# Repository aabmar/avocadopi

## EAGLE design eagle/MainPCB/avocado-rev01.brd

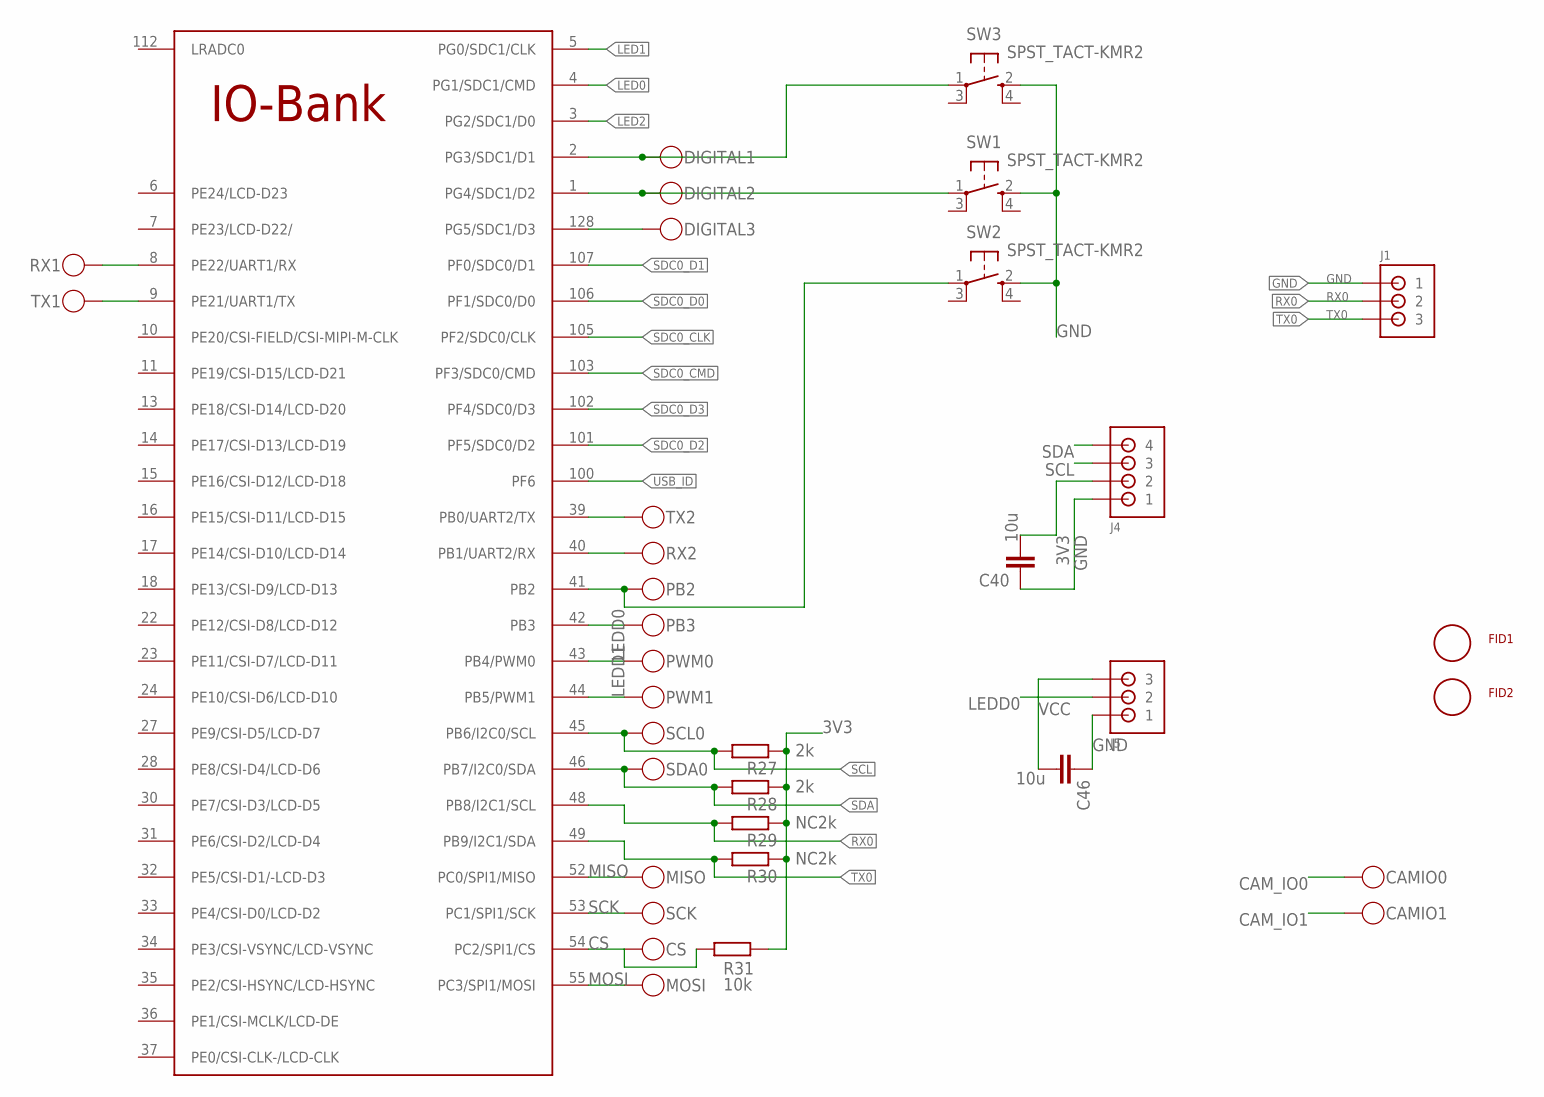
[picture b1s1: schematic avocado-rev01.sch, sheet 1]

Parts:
C40, C46: 10u; C0603
CAMIO0, CAMIO1: TEST_TESTPOINT
CS: TEST_TESTPOINT
DIGITAL1, DIGITAL2, DIGITAL3: TEST_TESTPOINT
FID1, FID2: FIDUCIAL; FIDUCIAL_1MM
J1, J5: CONNECTOR-3HEADER3; HEADER-3
J4: CONNECTOR-4HEADER4; HEADER-4
MISO: TEST_TESTPOINT
MOSI: TEST_TESTPOINT
PB2, PB3: TEST_TESTPOINT
PWM0, PWM1: TEST_TESTPOINT
R27, R28: 2k; R0402
R29, R30: NC2k; R0402
R31: 10k; R0402
RX1, RX2: TEST_TESTPOINT
SCK: TEST_TESTPOINT
SCL0: TEST_TESTPOINT
SDA0: TEST_TESTPOINT
SW1, SW2, SW3: SPST_TACT-KMR2; KMR2
TX1, TX2: TEST_TESTPOINT
U1: V3S; QFP-128

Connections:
3V3: C40.2, J4.2, R27.1, R28.1, R29.1, R30.1, R31.1; also elsewhere on the board
CAM_IO0: CAMIO0.1; also elsewhere on the board
CAM_IO1: CAMIO1.1; also elsewhere on the board
CS: CS.1, R31.2, U1.54 (PC2/SPI1/CS)
GND: C40.1, C46.1, J1.1, J4.1, J5.1, SW1.2 (S), SW2.2 (S), SW3.2 (S); also elsewhere on the board
LED0: U1.4 (PG1/SDC1/CMD); also elsewhere on the board
LED1: U1.5 (PG0/SDC1/CLK); also elsewhere on the board
LED2: U1.3 (PG2/SDC1/D0); also elsewhere on the board
LEDD0: J5.2, PWM0.1, U1.43 (PB4/PWM0); also elsewhere on the board
LEDD1: PWM1.1, U1.44 (PB5/PWM1); also elsewhere on the board
MISO: MISO.1, U1.52 (PC0/SPI1/MISO)
MOSI: MOSI.1, U1.55 (PC3/SPI1/MOSI)
unnamed: RX2.1, U1.40 (PB1/UART2/RX)
unnamed: PB2.1, SW2.1, U1.41 (PB2)
unnamed: PB3.1, U1.42 (PB3)
unnamed: DIGITAL1.1, SW3.1, U1.2 (PG3/SDC1/D1)
unnamed: DIGITAL2.1, SW1.1, U1.1 (PG4/SDC1/D2)
unnamed: DIGITAL3.1, U1.128 (PG5/SDC1/D3)
RX0: J1.2, R29.2, U1.48 (PB8/I2C1/SCL)
RX1: RX1.1, U1.8 (PE22/UART1/RX)
SCK: SCK.1, U1.53 (PC1/SPI1/SCK)
SCL: J4.3, R27.2, SCL0.1, U1.45 (PB6/I2C0/SCL); also elsewhere on the board
SDA: J4.4, R28.2, SDA0.1, U1.46 (PB7/I2C0/SDA); also elsewhere on the board
SDC0_CLK: U1.105 (PF2/SDC0/CLK); also elsewhere on the board
SDC0_CMD: U1.103 (PF3/SDC0/CMD); also elsewhere on the board
SDC0_D0: U1.106 (PF1/SDC0/D0); also elsewhere on the board
SDC0_D1: U1.107 (PF0/SDC0/D1); also elsewhere on the board
SDC0_D2: U1.101 (PF5/SDC0/D2); also elsewhere on the board
SDC0_D3: U1.102 (PF4/SDC0/D3); also elsewhere on the board
TX0: J1.3, R30.2, U1.49 (PB9/I2C1/SDA)
TX1: TX1.1, U1.9 (PE21/UART1/TX)
TX2: TX2.1, U1.39 (PB0/UART2/TX)
USB_ID: U1.100 (PF6); also elsewhere on the board
VCC: C46.2, J5.3; also elsewhere on the board

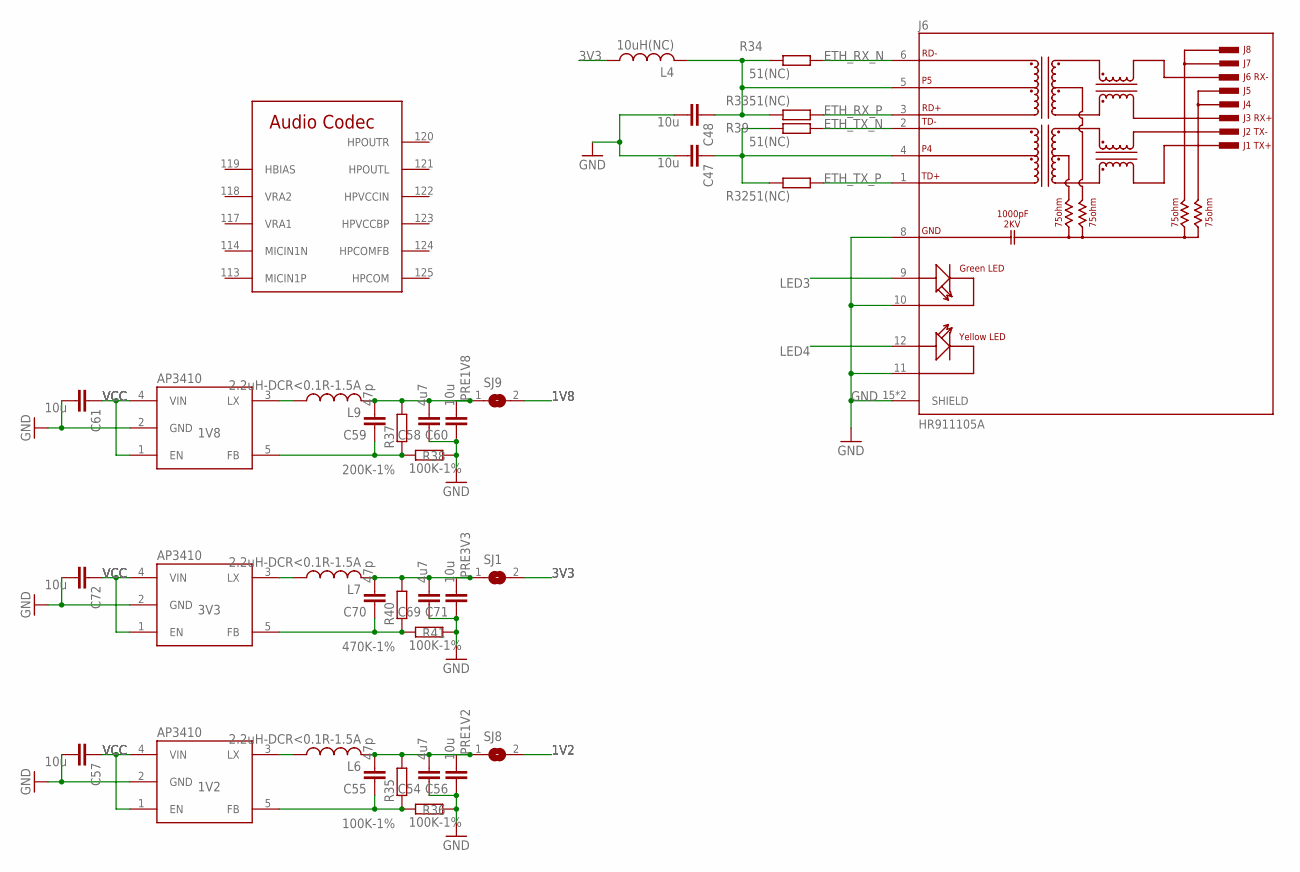
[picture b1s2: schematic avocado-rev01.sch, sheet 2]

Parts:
C47, C48, C56, C57, C60, C61, C71, C72: 10u; C0603
C54, C58, C69: 4u7; C0603
C55, C59, C70: 47p; C0603
IC2: 3V#; SOT23-5L; VOLTAGE 3V3; MPN AP3410KTR-G1
IC5: 3V#; SOT23-5L; VOLTAGE 1V2
IC6: MCP73811/2; SOT23-5L; VOLTAGE 1V8; MPN AP3410KTR-G1
J6: HR911105A; HANRUN_HR911105A
L4: 10uH(NC); R0603; MPN LVF404018-2R2M-N
L6, L7, L9: 2.2uH-DCR<0.1R-1.5A; ASPI-4030S-253675; MPN LVF404018-2R2M-N; MOUSER LVF404018-2R2M-N
R32, R33, R34, R39: 51(NC); R0402
R35, R36, R38, R41: 100K-1%; R0402
R37: 200K-1%; R0402
R40: 470K-1%; R0402
SJ1, SJ8, SJ9: SJ
U1: V3S; QFP-128

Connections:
1V2: SJ8.2; also elsewhere on the board
1V8: SJ9.2; also elsewhere on the board
3V3: L4.1, SJ1.2; also elsewhere on the board
ETH_RX_N: J6.6 (RD-), R34.1; also elsewhere on the board
ETH_RX_P: J6.3 (RD+), R33.1; also elsewhere on the board
ETH_TX_N: J6.2 (TD-), R39.1; also elsewhere on the board
ETH_TX_P: J6.1 (TD+), R32.1; also elsewhere on the board
GND: C47.2, C48.2, C54.1, C56.1, C57.2, C58.1, C60.1, C61.2, C69.1, C71.1, C72.2, IC2.2 (GND), IC5.2 (GND), IC6.2 (GND), J6.8 (GND), J6.10 (GC), J6.11 (YC), J6.15 (SHIELD), J6.16 (SHIELD), R36.2, R38.2, R41.2; also elsewhere on the board
LED3: J6.9 (GA); also elsewhere on the board
LED4: J6.12 (YA); also elsewhere on the board
unnamed: IC2.3 (LX), L7.P$1 (1)
unnamed: C70.1, IC2.5 (FB), R40.1, R41.1
unnamed: IC5.3 (LX), L6.P$1 (1)
unnamed: C55.1, IC5.5 (FB), R35.1, R36.1
unnamed: IC6.3 (LX), L9.P$1 (1)
unnamed: C59.1, IC6.5 (FB), R37.1, R38.1
unnamed: C47.1, J6.4, R32.2, R39.2
unnamed: C48.1, J6.5, L4.2, R33.2, R34.2
PRE1V2: C54.2, C55.2, C56.2, L6.P$2 (2), R35.2, SJ8.1
PRE1V8: C58.2, C59.2, C60.2, L9.P$2 (2), R37.2, SJ9.1
PRE3V3: C69.2, C70.2, C71.2, L7.P$2 (2), R40.2, SJ1.1
VCC: C57.1, C61.1, C72.1, IC2.1 (EN), IC2.4 (VIN), IC5.1 (EN), IC5.4 (VIN), IC6.1 (EN), IC6.4 (VIN); also elsewhere on the board

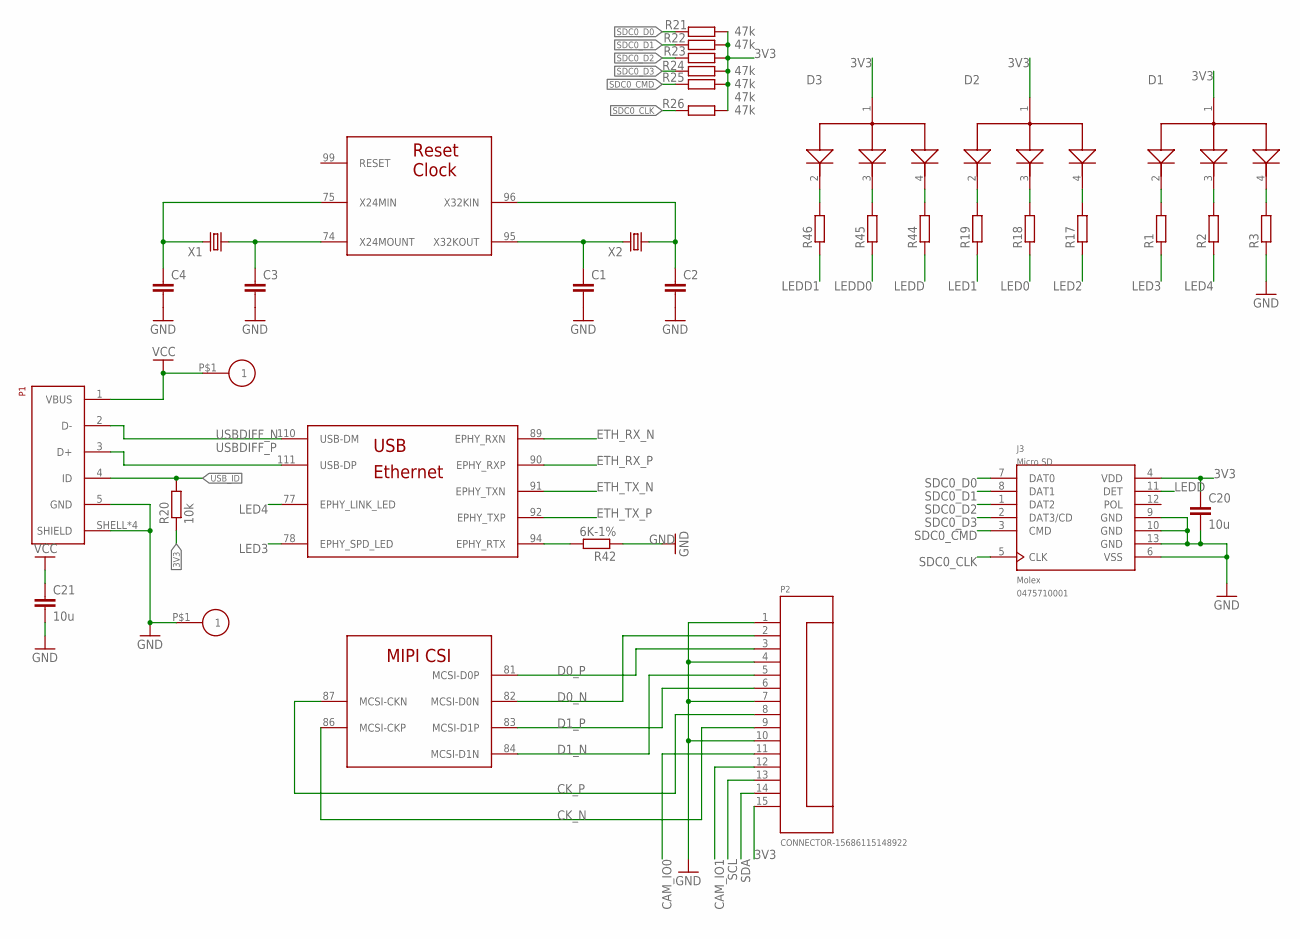
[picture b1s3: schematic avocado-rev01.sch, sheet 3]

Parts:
5V: PADTH; PAD
C1, C2, C3, C4: C0603
C20, C21: 10u; C0603
D1, D2, D3: LL-R3528RGBC-008-B; LED_LL-R3528RGBC-008-B; MPN HQ67-23A2ARGBC
GND: PADTH; PAD
J3: 0475710001; MOLEX_0475710001
P1: USB629105150521; 629105150521
P2: CONNECTOR-15686115148922; 686115148922
R1, R2, R3, R17, R18, R19, R44, R45, R46: R-EU_R0402; R0402
R20: 10k; R0402
R21, R22, R23, R24, R25, R26: 47k; R0603
R42: 6K-1%; R0402
U1: V3S; QFP-128
X1: XTAL3.2X2; 3.2X2-4; MPN 7U24000E09UCG
X2: XTAL5X1.9; XTAL-5X1.9; MPN SF32K32768D71T01

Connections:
3V3: C20.1, D1.1 (COMM_ANODE), D2.1 (COMM_ANODE), D3.1 (COMM_ANODE), J3.4 (VDD), P2.15, R20.1, R21.2, R22.2, R23.2, R24.2, R25.2, R26.2; also elsewhere on the board
CAM_IO0: P2.11; also elsewhere on the board
CAM_IO1: P2.12; also elsewhere on the board
CK_N: P2.9, U1.86 (MCSI-CKP)
CK_P: P2.8, U1.87 (MCSI-CKN)
D0_N: P2.2, U1.82 (MCSI-D0N)
D0_P: P2.3, U1.81 (MCSI-D0P)
D1_N: P2.5, U1.84 (MCSI-D1N)
D1_P: P2.6, U1.83 (MCSI-D1P)
ETH_RX_N: U1.89 (EPHY_RXN); also elsewhere on the board
ETH_RX_P: U1.90 (EPHY_RXP); also elsewhere on the board
ETH_TX_N: U1.91 (EPHY_TXN); also elsewhere on the board
ETH_TX_P: U1.92 (EPHY_TXP); also elsewhere on the board
GND: C1.2, C2.2, C3.2, C4.2, C20.2, C21.2, GND.P$1, J3.6 (VSS), J3.9 (GND), J3.10 (GND), J3.13 (GND), P1.5 (GND), P1.SHELL (SHIELD), P1.SHELL1 (SHIELD), P1.SHELL2 (SHIELD), P1.SHELL3 (SHIELD), P2.1, P2.4, P2.7, P2.10, R3.1, R42.1; also elsewhere on the board
LED0: R18.1; also elsewhere on the board
LED1: R19.1; also elsewhere on the board
LED2: R17.1; also elsewhere on the board
LED3: R1.1, U1.78 (EPHY_SPD_LED); also elsewhere on the board
LED4: R2.1, U1.77 (EPHY_LINK_LED); also elsewhere on the board
LEDD: J3.11 (DET), R44.1
LEDD0: R45.1; also elsewhere on the board
LEDD1: R46.1; also elsewhere on the board
unnamed: C4.1, U1.75 (X24MIN), X1.P$3 (2)
unnamed: C3.1, U1.74 (X24MOUNT), X1.P$1 (1)
unnamed: C1.1, U1.95 (X32KOUT), X2.P$2 (2)
unnamed: C2.1, U1.96 (X32KIN), X2.P$1 (1)
unnamed: D2.2 (CATHODE_RED), R19.2
unnamed: D2.3 (CATHODE_GREEN), R18.2
unnamed: D2.4 (CATHODE_BLUE), R17.2
unnamed: D1.2 (CATHODE_RED), R1.2
unnamed: D1.3 (CATHODE_GREEN), R2.2
unnamed: D1.4 (CATHODE_BLUE), R3.2
unnamed: R42.2, U1.94 (EPHY_RTX)
unnamed: D3.2 (CATHODE_RED), R46.2
unnamed: D3.3 (CATHODE_GREEN), R45.2
unnamed: D3.4 (CATHODE_BLUE), R44.2
SCL: P2.13; also elsewhere on the board
SDA: P2.14; also elsewhere on the board
SDC0_CLK: J3.5 (CLK), R26.1; also elsewhere on the board
SDC0_CMD: J3.3 (CMD), R25.1; also elsewhere on the board
SDC0_D0: J3.7 (DAT0), R21.1; also elsewhere on the board
SDC0_D1: J3.8 (DAT1), R22.1; also elsewhere on the board
SDC0_D2: J3.1 (DAT2), R23.1; also elsewhere on the board
SDC0_D3: J3.2 (DAT3/CD), R24.1; also elsewhere on the board
USBDIFF_N: P1.2 (D-), U1.110 (USB-DM)
USBDIFF_P: P1.3 (D+), U1.111 (USB-DP)
USB_ID: P1.4 (ID), R20.2; also elsewhere on the board
VCC: 5V.P$1, C21.1, P1.1 (VBUS); also elsewhere on the board

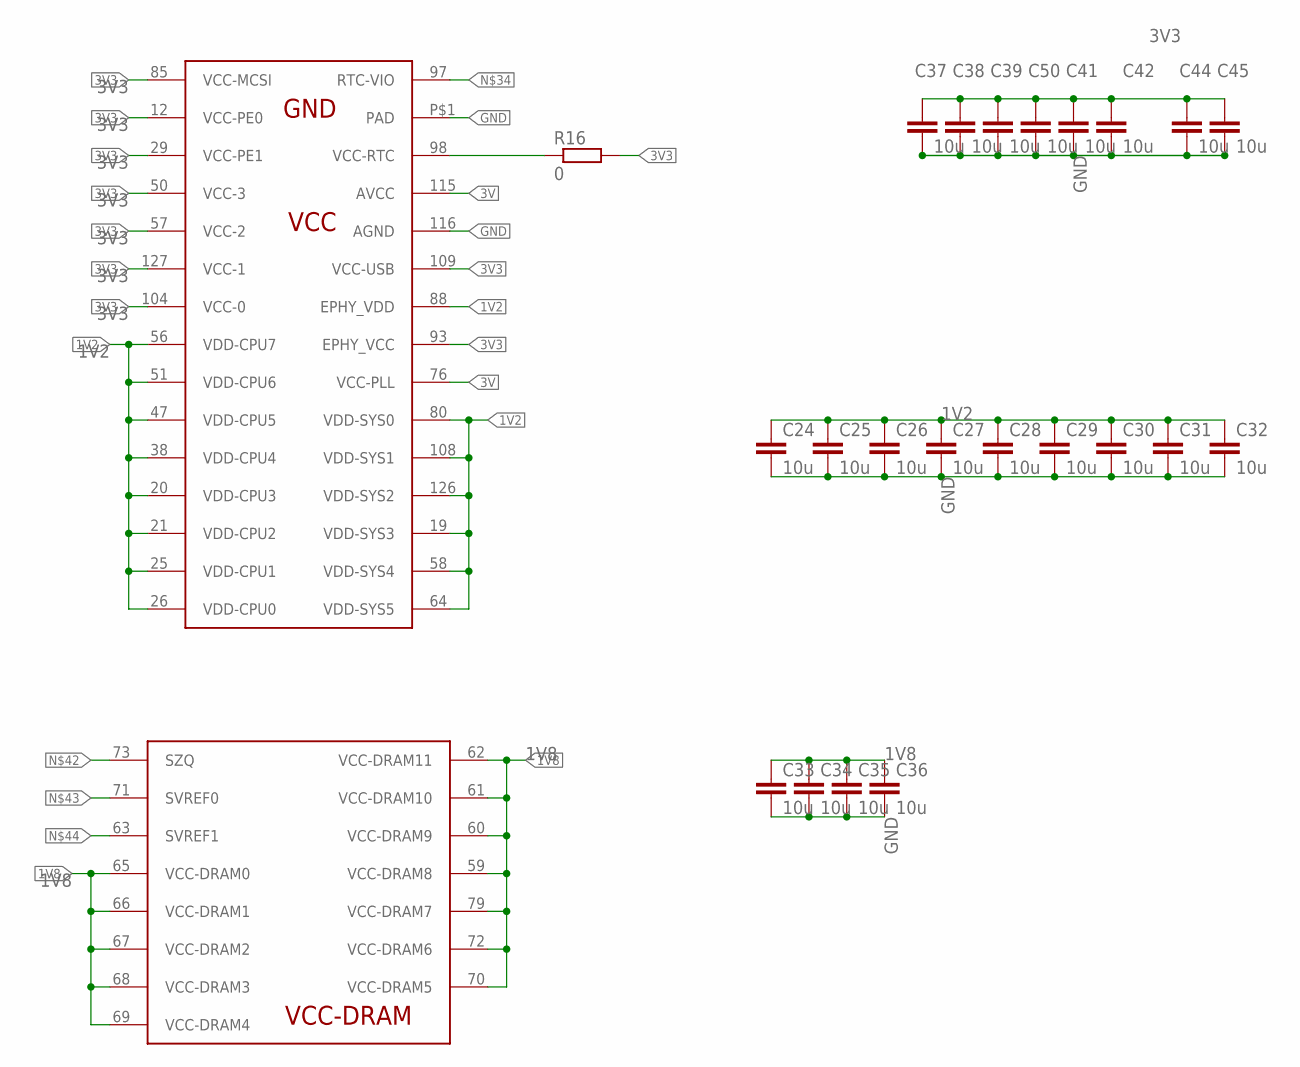
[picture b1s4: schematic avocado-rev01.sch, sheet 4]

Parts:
C24, C25, C26, C27, C28, C29, C30, C31, C32, C33, C34, C35, C36, C37, C38, C39, C41, C42, C44, C45, C50: 10u; C0603
R16: 0; R0603
U1: V3S; QFP-128

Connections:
1V2: C24.1, C25.1, C26.1, C27.1, C28.1, C29.1, C30.1, C31.1, C32.1, U1.19 (VDD-SYS3), U1.20 (VDD-CPU3), U1.21 (VDD-CPU2), U1.25 (VDD-CPU1), U1.26 (VDD-CPU0), U1.38 (VDD-CPU4), U1.47 (VDD-CPU5), U1.51 (VDD-CPU6), U1.56 (VDD-CPU7), U1.58 (VDD-SYS4), U1.64 (VDD-SYS5), U1.80 (VDD-SYS0), U1.88 (EPHY_VDD), U1.108 (VDD-SYS1), U1.126 (VDD-SYS2); also elsewhere on the board
1V8: C33.1, C34.1, C35.1, C36.1, U1.59 (VCC-DRAM8), U1.60 (VCC-DRAM9), U1.61 (VCC-DRAM10), U1.62 (VCC-DRAM11), U1.65 (VCC-DRAM0), U1.66 (VCC-DRAM1), U1.67 (VCC-DRAM2), U1.68 (VCC-DRAM3), U1.69 (VCC-DRAM4), U1.70 (VCC-DRAM5), U1.72 (VCC-DRAM6), U1.79 (VCC-DRAM7); also elsewhere on the board
3V: U1.76 (VCC-PLL), U1.115 (AVCC); also elsewhere on the board
3V3: C37.1, C38.1, C39.1, C41.1, C42.1, C44.1, C45.1, C50.1, R16.2, U1.12 (VCC-PE0), U1.29 (VCC-PE1), U1.50 (VCC-3), U1.57 (VCC-2), U1.85 (VCC-MCSI), U1.93 (EPHY_VCC), U1.104 (VCC-0), U1.109 (VCC-USB), U1.127 (VCC-1); also elsewhere on the board
GND: C24.2, C25.2, C26.2, C27.2, C28.2, C29.2, C30.2, C31.2, C32.2, C33.2, C34.2, C35.2, C36.2, C37.2, C38.2, C39.2, C41.2, C42.2, C44.2, C45.2, C50.2, U1.116 (AGND), U1.P$1 (PAD); also elsewhere on the board
unnamed: R16.1, U1.98 (VCC-RTC)

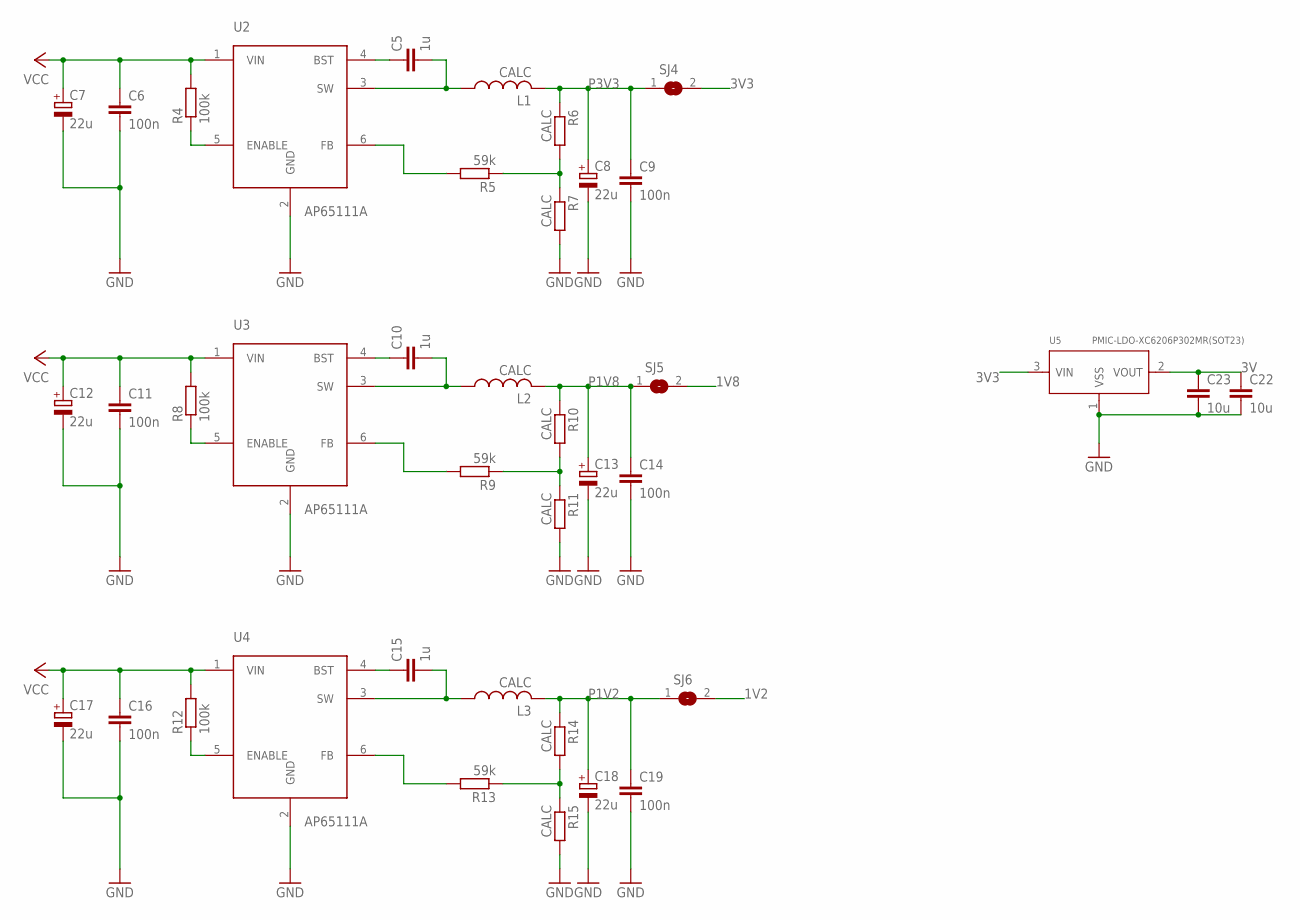
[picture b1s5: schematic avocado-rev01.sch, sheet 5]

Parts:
C5, C10, C15: 1u; C0603
C6, C9, C11, C14, C16, C19: 100n; C0603
C7, C8, C12, C13, C17, C18: 22u; CAP4.3X6.1
C22, C23: 10u; C0603
L1, L2, L3: CALC; B82462A4153K
R4, R8, R12: 100k; R0603
R5, R9, R13: 59k; R0603
R6, R7, R10, R11, R14, R15: CALC; R0603
SJ4, SJ5, SJ6: SJ
U2, U3, U4: AP65111A; TSOT26
U5: PMIC-LDO-XC6206P302MR(SOT23); SOT-23

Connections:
1V2: SJ6.2; also elsewhere on the board
1V8: SJ5.2; also elsewhere on the board
3V: C22.1, C23.1, U5.2 (VOUT); also elsewhere on the board
3V3: SJ4.2, U5.3 (VIN); also elsewhere on the board
GND: C6.2, C7.2 (-), C8.2 (-), C9.2, C11.2, C12.2 (-), C13.2 (-), C14.2, C16.2, C17.2 (-), C18.2 (-), C19.2, C22.2, C23.2, R7.2, R11.2, R15.2, U2.2 (GND), U3.2 (GND), U4.2 (GND), U5.1 (VSS); also elsewhere on the board
unnamed: R5.2, U2.6 (FB)
unnamed: C5.2, L1.P$1 (1), U2.3 (SW)
unnamed: R5.1, R6.2, R7.1
unnamed: C5.1, U2.4 (BST)
unnamed: R4.1, U2.5 (ENABLE)
unnamed: R9.2, U3.6 (FB)
unnamed: C10.2, L2.P$1 (1), U3.3 (SW)
unnamed: R9.1, R10.2, R11.1
unnamed: C10.1, U3.4 (BST)
unnamed: R8.1, U3.5 (ENABLE)
unnamed: R13.2, U4.6 (FB)
unnamed: C15.2, L3.P$1 (1), U4.3 (SW)
unnamed: R13.1, R14.2, R15.1
unnamed: C15.1, U4.4 (BST)
unnamed: R12.1, U4.5 (ENABLE)
P1V2: C18.1 (+), C19.1, L3.P$2 (2), R14.1, SJ6.1
P1V8: C13.1 (+), C14.1, L2.P$2 (2), R10.1, SJ5.1
P3V3: C8.1 (+), C9.1, L1.P$2 (2), R6.1, SJ4.1
VCC: C6.1, C7.1 (+), C11.1, C12.1 (+), C16.1, C17.1 (+), R4.2, R8.2, R12.2, U2.1 (VIN), U3.1 (VIN), U4.1 (VIN); also elsewhere on the board

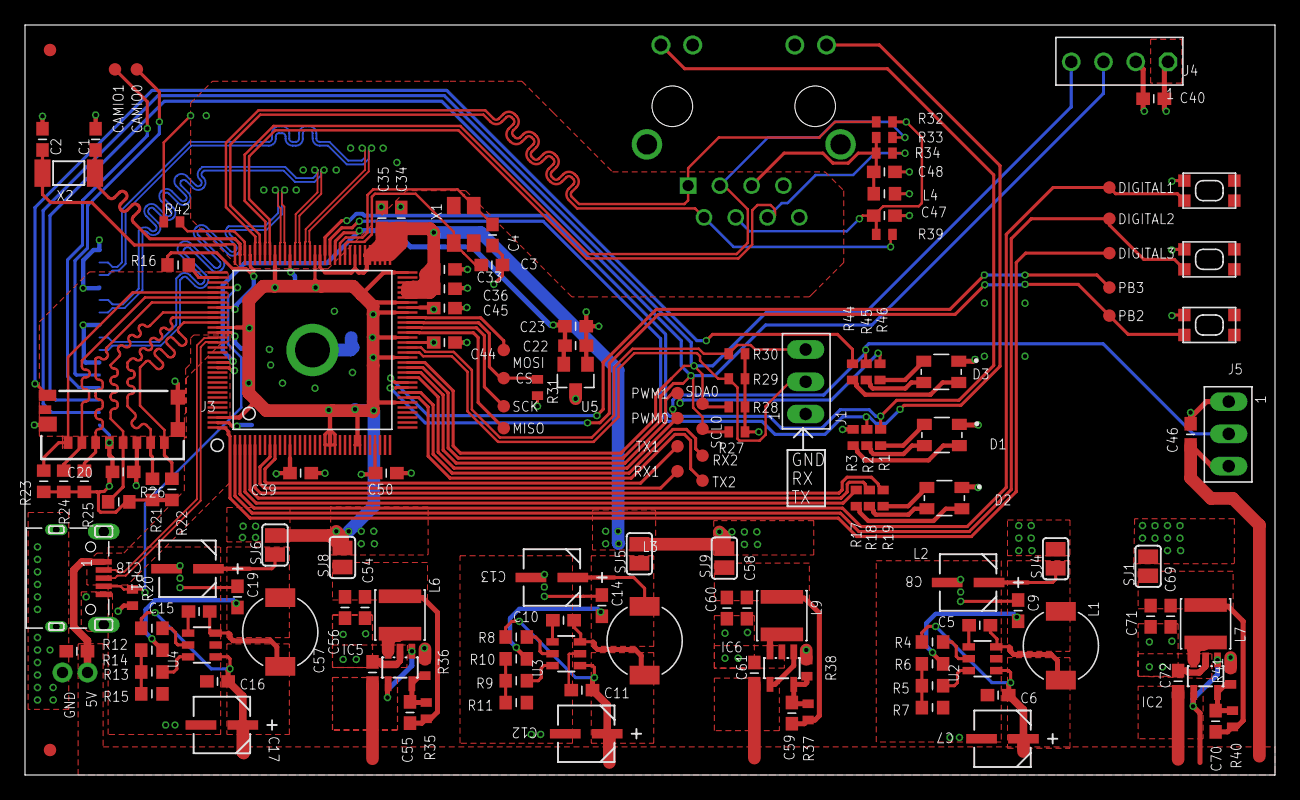
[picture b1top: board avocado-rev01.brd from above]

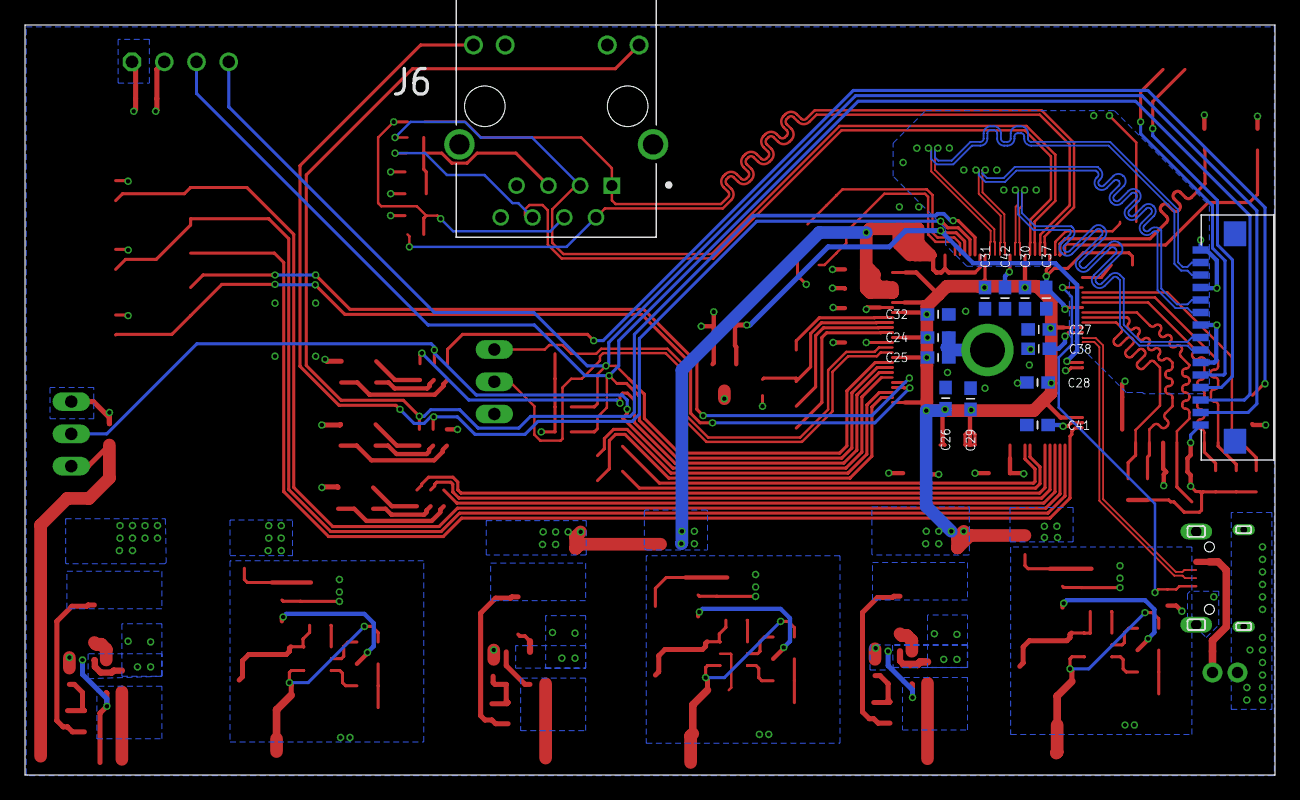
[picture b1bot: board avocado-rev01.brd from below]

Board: 4 copper layers, 100.0 x 60.0 mm, 164 parts (15 on the bottom side), 96 nets.

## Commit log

2019-02-23 Set up Schematics with V3s
2019-02-28 updated schematic
2019-02-28 Connected power
2019-02-28 Removed backup files
2019-03-01 connected sd card and added led
2019-03-01 added testpoints
2019-03-01 updated i2c
2019-03-04 connected psu in schem
2019-03-04 placement
2019-03-04 shitty routing v1
2019-03-06 accurate high speed routing, now 4 layer
2019-03-06 better routing v2
2019-03-06 better routing v3
2019-03-08 decoupling caps
2019-03-11 added 3V rail
2019-03-18 updated decoupling vias
2019-03-19 update keepout area
2019-03-21 add axp209
2019-03-21 updated values
2019-03-25 added jumpers
2019-03-25 high
2019-03-26 Added design rules
2019-03-26 working
2019-03-27 In progress
2019-04-11 Added gfx
2019-04-11 Changed usb connector
2019-04-13 Added server example, and a partial C implementation
2019-04-13 Added some gcode example files
2019-04-13 C and Python implementation for gcode analisys
2019-04-25 Added pin header for RX0/TX0
2019-04-25 Fixed some labels.
2019-04-25 CAM job
2019-04-27 added usb lib
2019-05-04 Changed 0402 to 0603, adjusted some line

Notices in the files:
parts and their libraries:
m-pad-2.1: License : GNU General Public License version 2 (see bottom)
